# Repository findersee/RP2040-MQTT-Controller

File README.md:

# Controller
<p>RP2040 MQTT Controller for DIN Rail</p>

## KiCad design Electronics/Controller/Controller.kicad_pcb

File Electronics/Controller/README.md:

# Controller
<p>RP2040 Ethernet board</p>

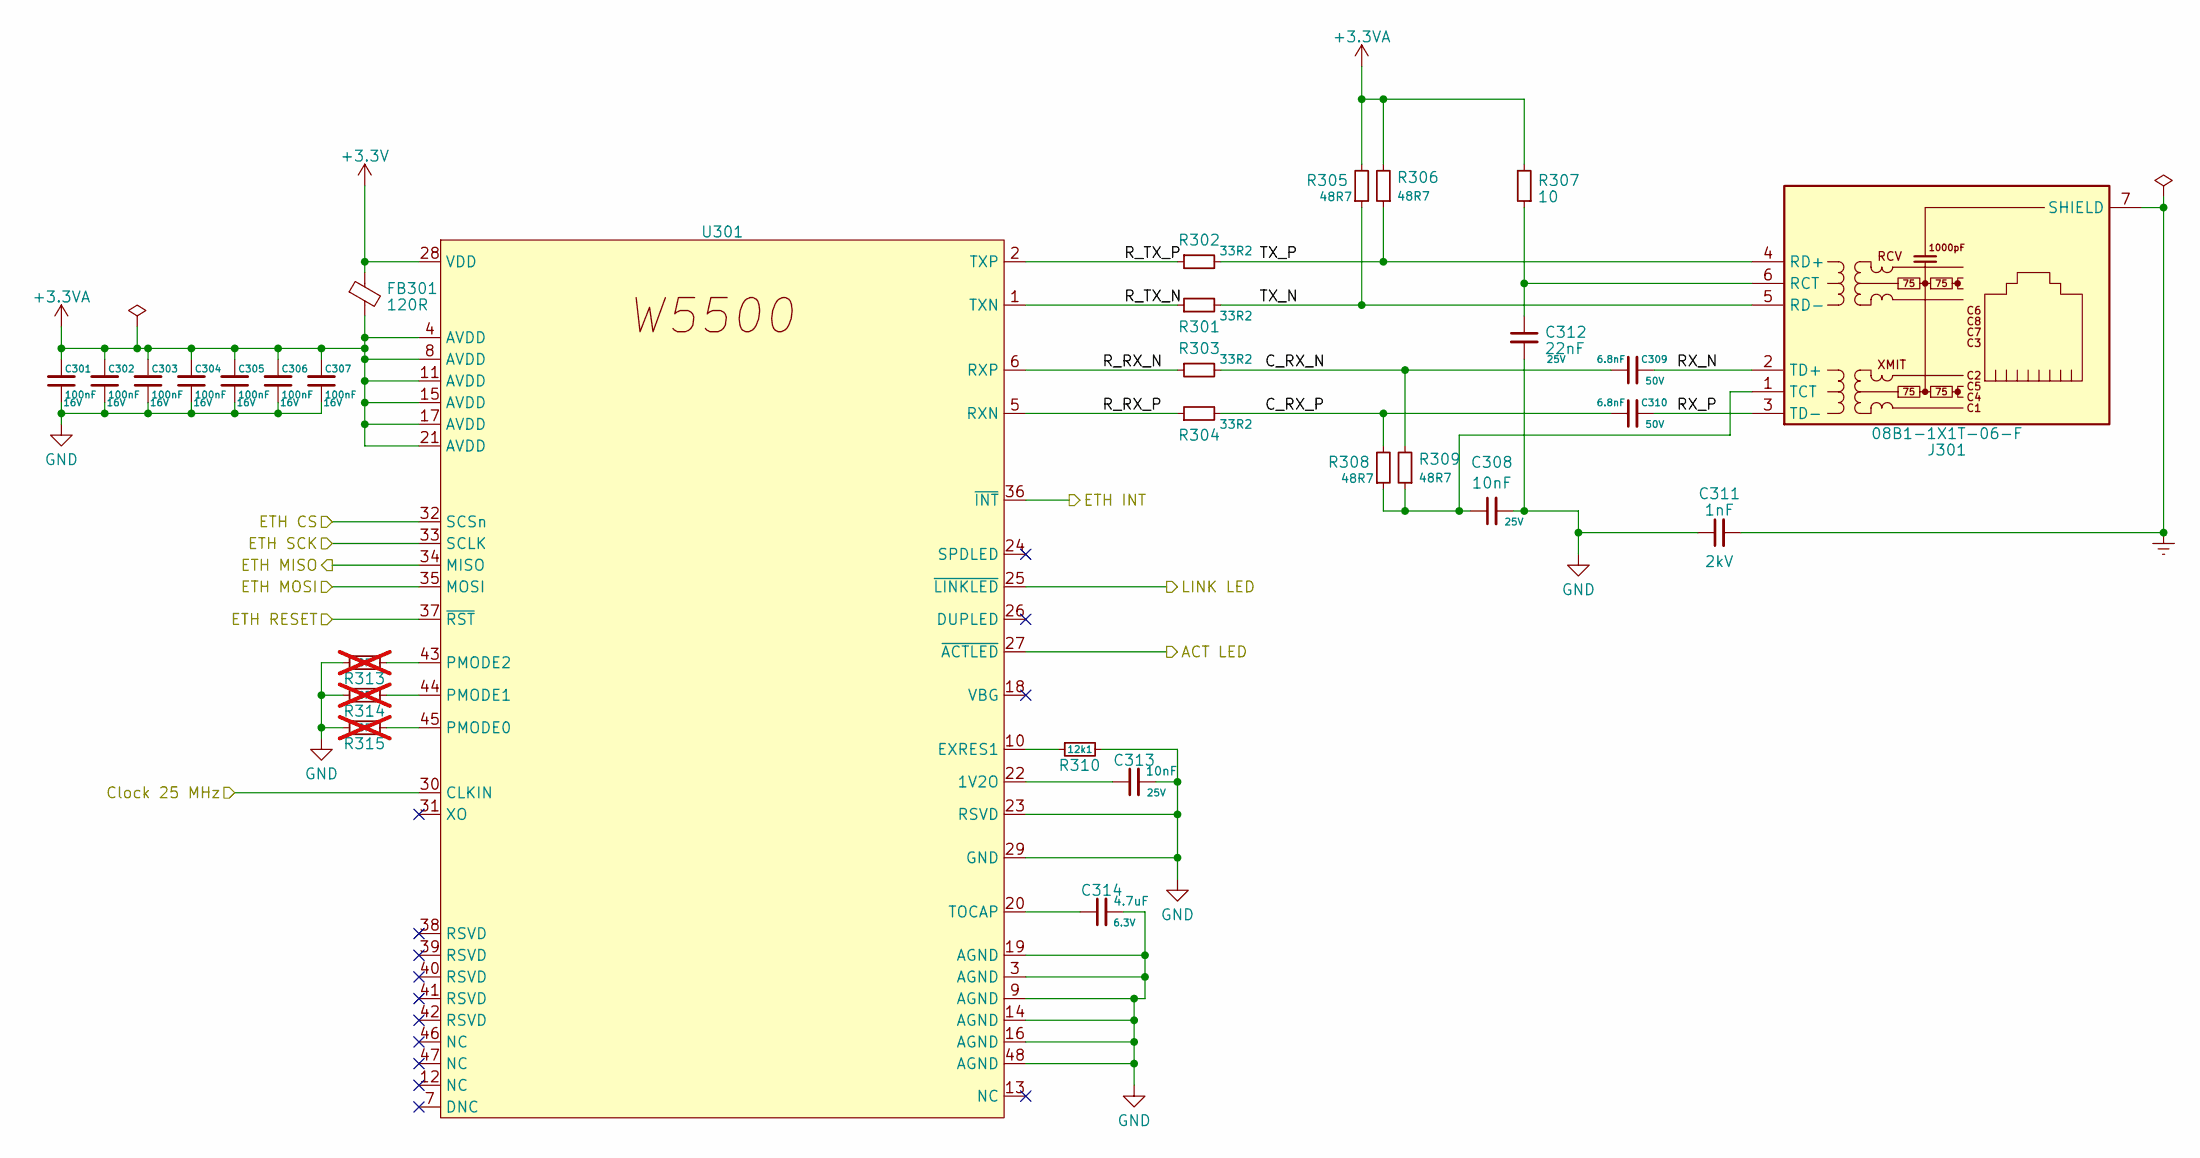
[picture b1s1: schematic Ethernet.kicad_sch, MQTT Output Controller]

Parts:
C301, C302, C303, C304, C305, C306, C307: 100nF; C_0402_1005Metric; Voltage 16V
C308, C313: 10nF; C_0402_1005Metric; Voltage 25V
C309, C310: 6.8nF; C_0402_1005Metric; Voltage 50V
C311: 1nF; C_1206_3216Metric; Voltage 2kV
C312: 22nF; C_0402_1005Metric; Voltage 25V
C314: 4.7uF; C_0402_1005Metric; Voltage 6.3V
FB301: 120R; R_0805_2012Metric
J301: 08B1-1X1T-06-F
R301, R302, R303, R304: 33R2; R_0402_1005Metric
R305, R306, R308, R309: 48R7; R_0402_1005Metric
R307: 10; R_0402_1005Metric
R310: 12k1; R_0402_1005Metric
R313, R314, R315: 0R; R_0402_1005Metric; not fitted
U301: W5500; TQFP-48_7x7mm_P0.5mm

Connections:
+3.3V: FB301.1, U301.28 (VDD); also elsewhere on the board
+3.3VA: C301.2, C302.2, C303.2, C304.2, C305.2, C306.2, C307.2, FB301.2, R305.2, R306.2, R307.2, U301.4 (AVDD), U301.8 (AVDD), U301.11 (AVDD), U301.15 (AVDD), U301.17 (AVDD), U301.21 (AVDD)
/Ethernet/ACT LED: U301.27 (~ACTLED); also elsewhere on the board
/Ethernet/C_RX_N: C309.1, R303.2, R309.2
/Ethernet/C_RX_P: C310.1, R304.2, R308.2
/Ethernet/Clock 25 MHz: U301.30 (CLKIN); also elsewhere on the board
/Ethernet/ETH CS: U301.32 (SCSn); also elsewhere on the board
/Ethernet/ETH INT: U301.36 (~INT); also elsewhere on the board
/Ethernet/ETH MISO: U301.34 (MISO); also elsewhere on the board
/Ethernet/ETH MOSI: U301.35 (MOSI); also elsewhere on the board
/Ethernet/ETH RESET: U301.37 (~RST); also elsewhere on the board
/Ethernet/ETH SCK: U301.33 (SCLK); also elsewhere on the board
/Ethernet/LINK LED: U301.25 (~LINKLED); also elsewhere on the board
/Ethernet/RX_N: C309.2, J301.2 (TD+)
/Ethernet/RX_P: C310.2, J301.3 (TD-)
/Ethernet/R_RX_N: R303.1, U301.6 (RXP)
/Ethernet/R_RX_P: R304.1, U301.5 (RXN)
/Ethernet/R_TX_N: R301.1, U301.1 (TXN)
/Ethernet/R_TX_P: R302.1, U301.2 (TXP)
/Ethernet/TX_N: J301.5 (RD-), R301.2, R305.1
/Ethernet/TX_P: J301.4 (RD+), R302.2, R306.1
Earth: C311.2, J301.7 (SHIELD); also elsewhere on the board
GND: C301.1, C302.1, C303.1, C304.1, C305.1, C306.1, C307.1, C308.2, C311.1, C312.2, C313.2, C314.2, R310.2, R313.1, R314.1, R315.1, U301.3 (AGND), U301.9 (AGND), U301.14 (AGND), U301.16 (AGND), U301.19 (AGND), U301.23 (RSVD), U301.29 (GND), U301.48 (AGND); also elsewhere on the board
unnamed: C312.1, J301.6 (RCT), R307.1
unnamed: C308.1, J301.1 (TCT), R308.1, R309.1
unnamed: C313.1, U301.22 (1V2O)
unnamed: R310.1, U301.10 (EXRES1)
unnamed: R315.2, U301.45 (PMODE0)
unnamed: R314.2, U301.44 (PMODE1)
unnamed: R313.2, U301.43 (PMODE2)
unnamed: C314.1, U301.20 (TOCAP)

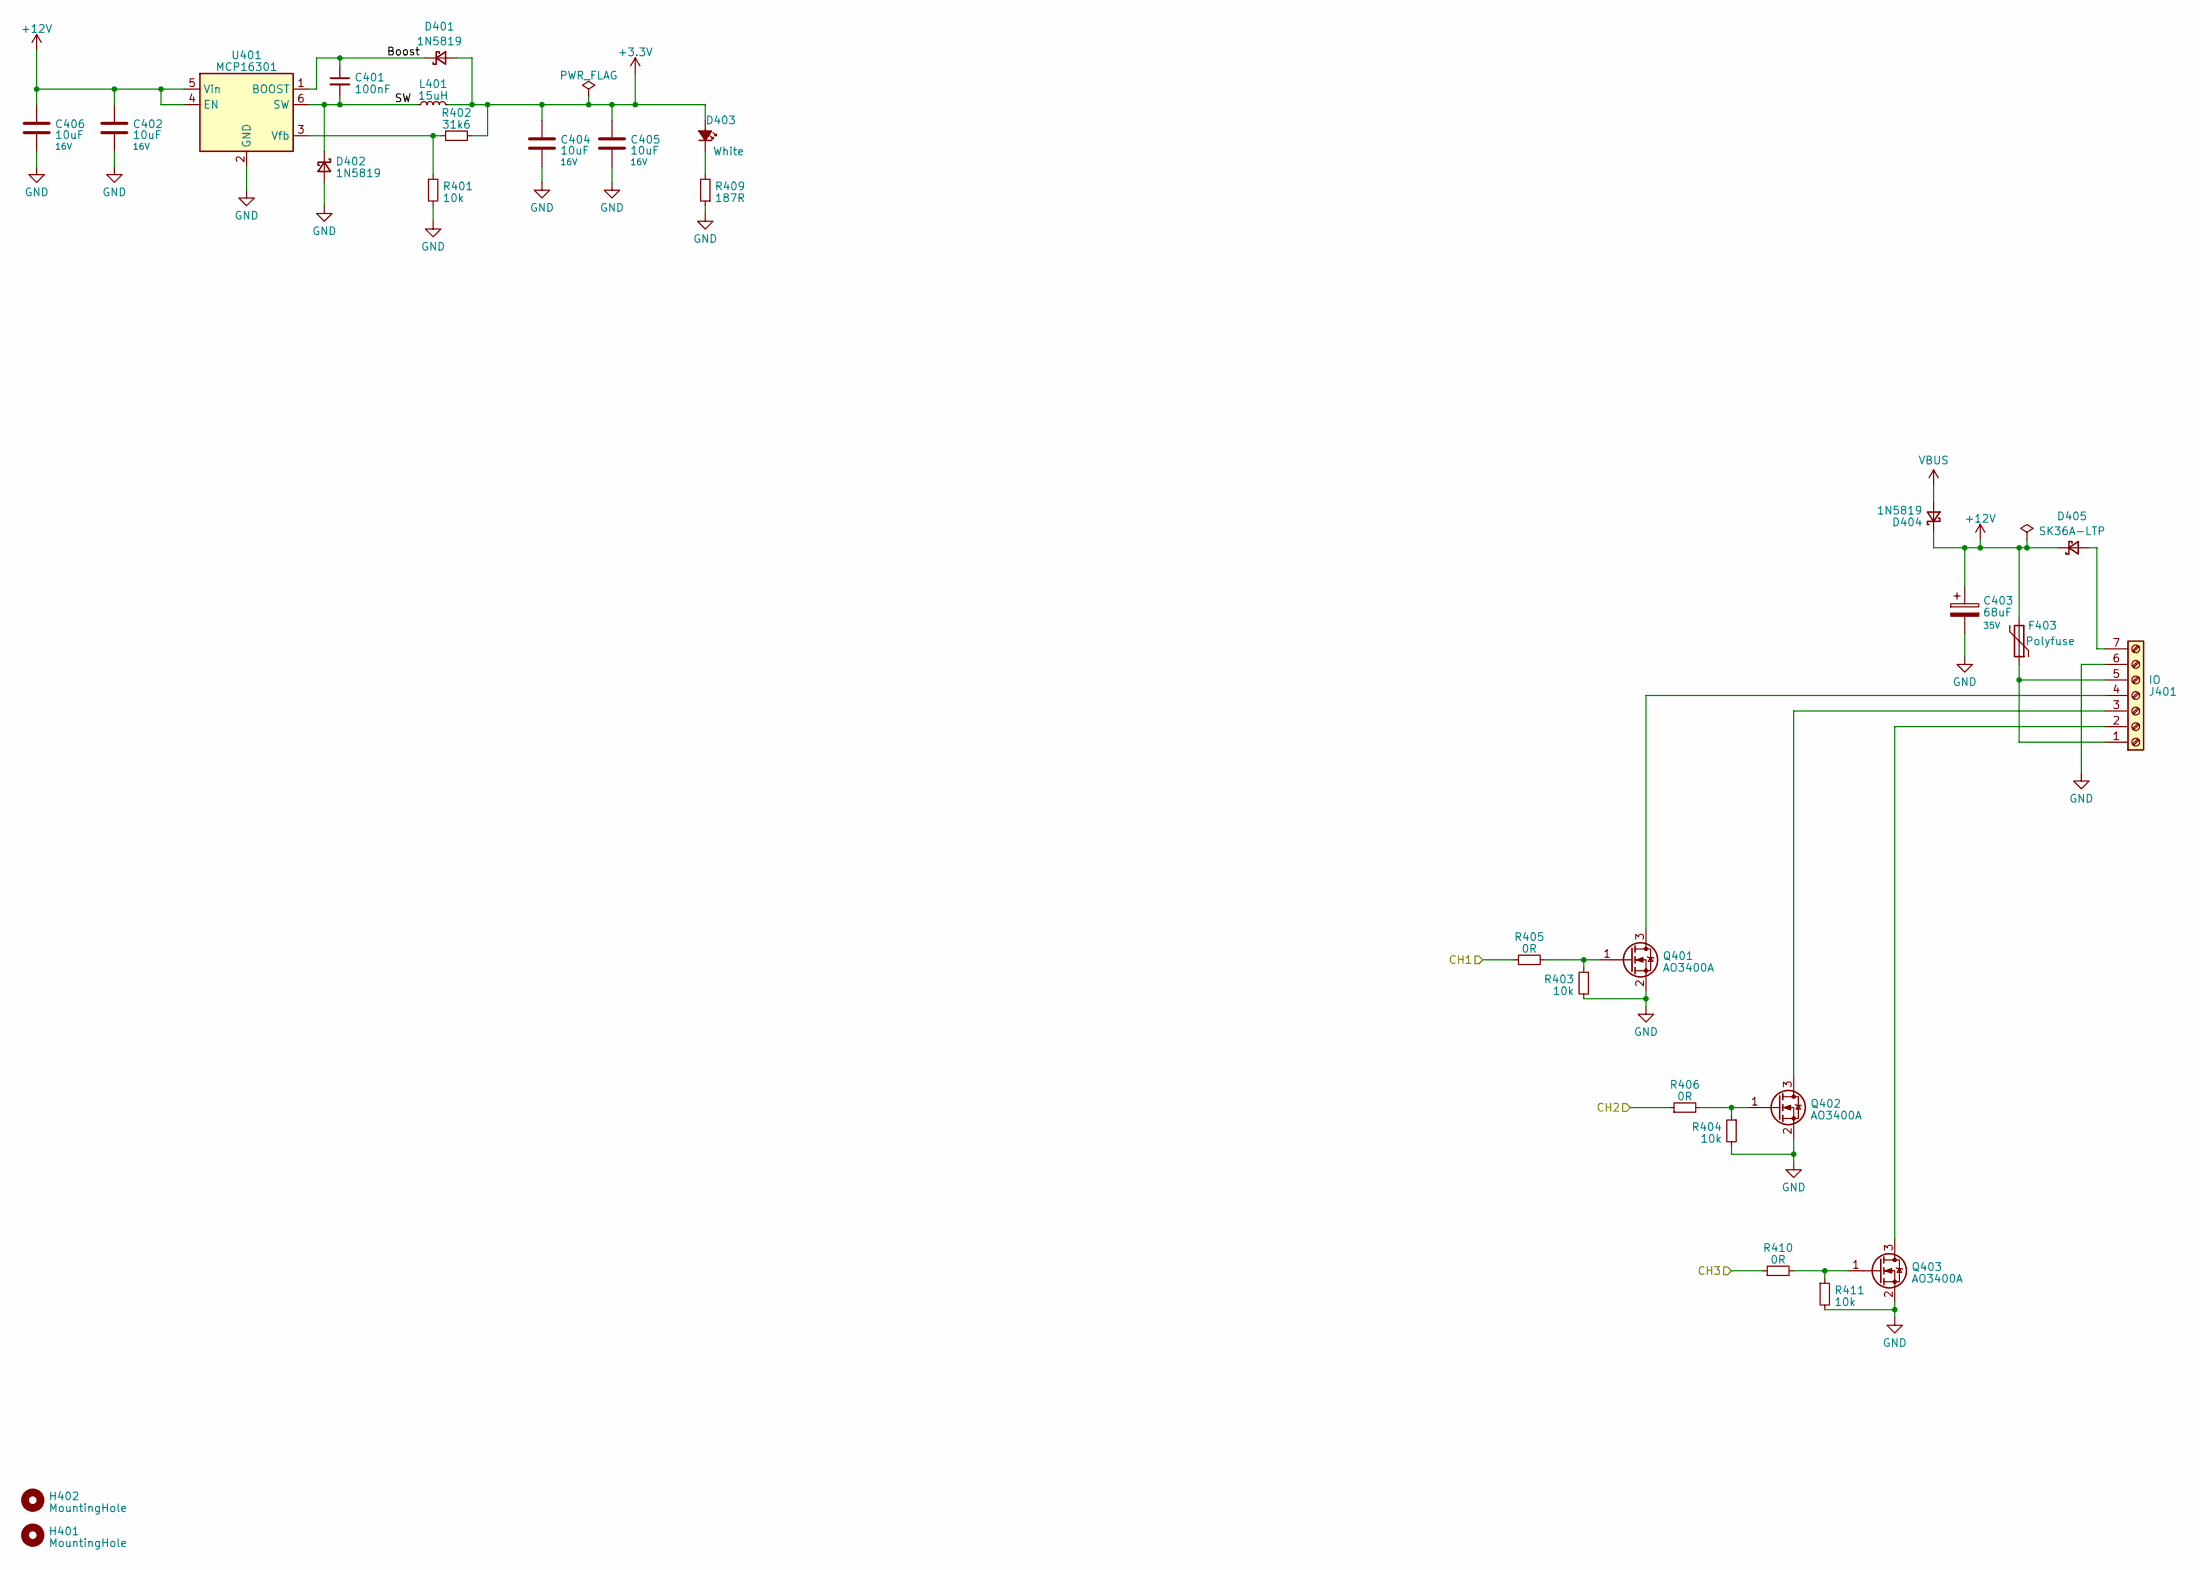
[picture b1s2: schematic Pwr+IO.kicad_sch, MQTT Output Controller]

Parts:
C401: 100nF; C_0402_1005Metric
C402, C404, C405, C406: 10uF; C_0805_2012Metric; Voltage 16V
C403: 68uF; CP_Elec_6.3x5.8; Voltage 35V
D401, D402, D404: 1N5819; D_SOD-123
D403: White; LED_0603_1608Metric
D405: SK36A-LTP; D_SMA
F403: Polyfuse; Fuse_BelFuse_0ZRE0005FF_L8.3mm_W3.8mm
H401, H402: MountingHole; MountingHole_2.5mm
J401: IO; Terminal-Block-01x07_P3.81
L401: 15uH; L_Coilcraft_LPS3010
Q401, Q402, Q403: AO3400A; SOT-23
R401, R403, R404, R411: 10k; R_0402_1005Metric
R402: 31k6; R_0402_1005Metric
R405, R406, R410: 0R; R_0402_1005Metric
R409: 187R; R_0402_1005Metric
U401: MCP16301; SOT-23-6

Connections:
+3.3V: C404.1, C405.1, D401.2 (A), D403.2 (A), L401.2, R402.2; also elsewhere on the board
+12V: C402.1, C403.1, C406.1, D404.1 (K), D405.1 (K), F403.2, U401.4 (EN), U401.5 (Vin)
/Power and Output/Boost: C401.1, D401.1 (K), U401.1 (BOOST)
/Power and Output/CH1: R405.1; also elsewhere on the board
/Power and Output/CH2: R406.1; also elsewhere on the board
/Power and Output/CH3: R410.1; also elsewhere on the board
/Power and Output/SW: C401.2, D402.1 (K), L401.1, U401.6 (SW)
GND: C402.2, C403.2, C404.2, C405.2, C406.2, D402.2 (A), J401.6, Q401.2 (S), Q402.2 (S), Q403.2 (S), R401.2, R403.2, R404.2, R409.1, R411.2, U401.2 (GND); also elsewhere on the board
unnamed: D403.1 (K), R409.2
unnamed: D405.2 (A), J401.7
unnamed: F403.1, J401.1, J401.5
unnamed: J401.2, Q403.3 (D)
unnamed: J401.3, Q402.3 (D)
unnamed: J401.4, Q401.3 (D)
unnamed: Q401.1 (G), R403.1, R405.2
unnamed: Q402.1 (G), R404.1, R406.2
unnamed: Q403.1 (G), R410.2, R411.1
unnamed: R401.1, R402.1, U401.3 (Vfb)
VBUS: D404.2 (A); also elsewhere on the board

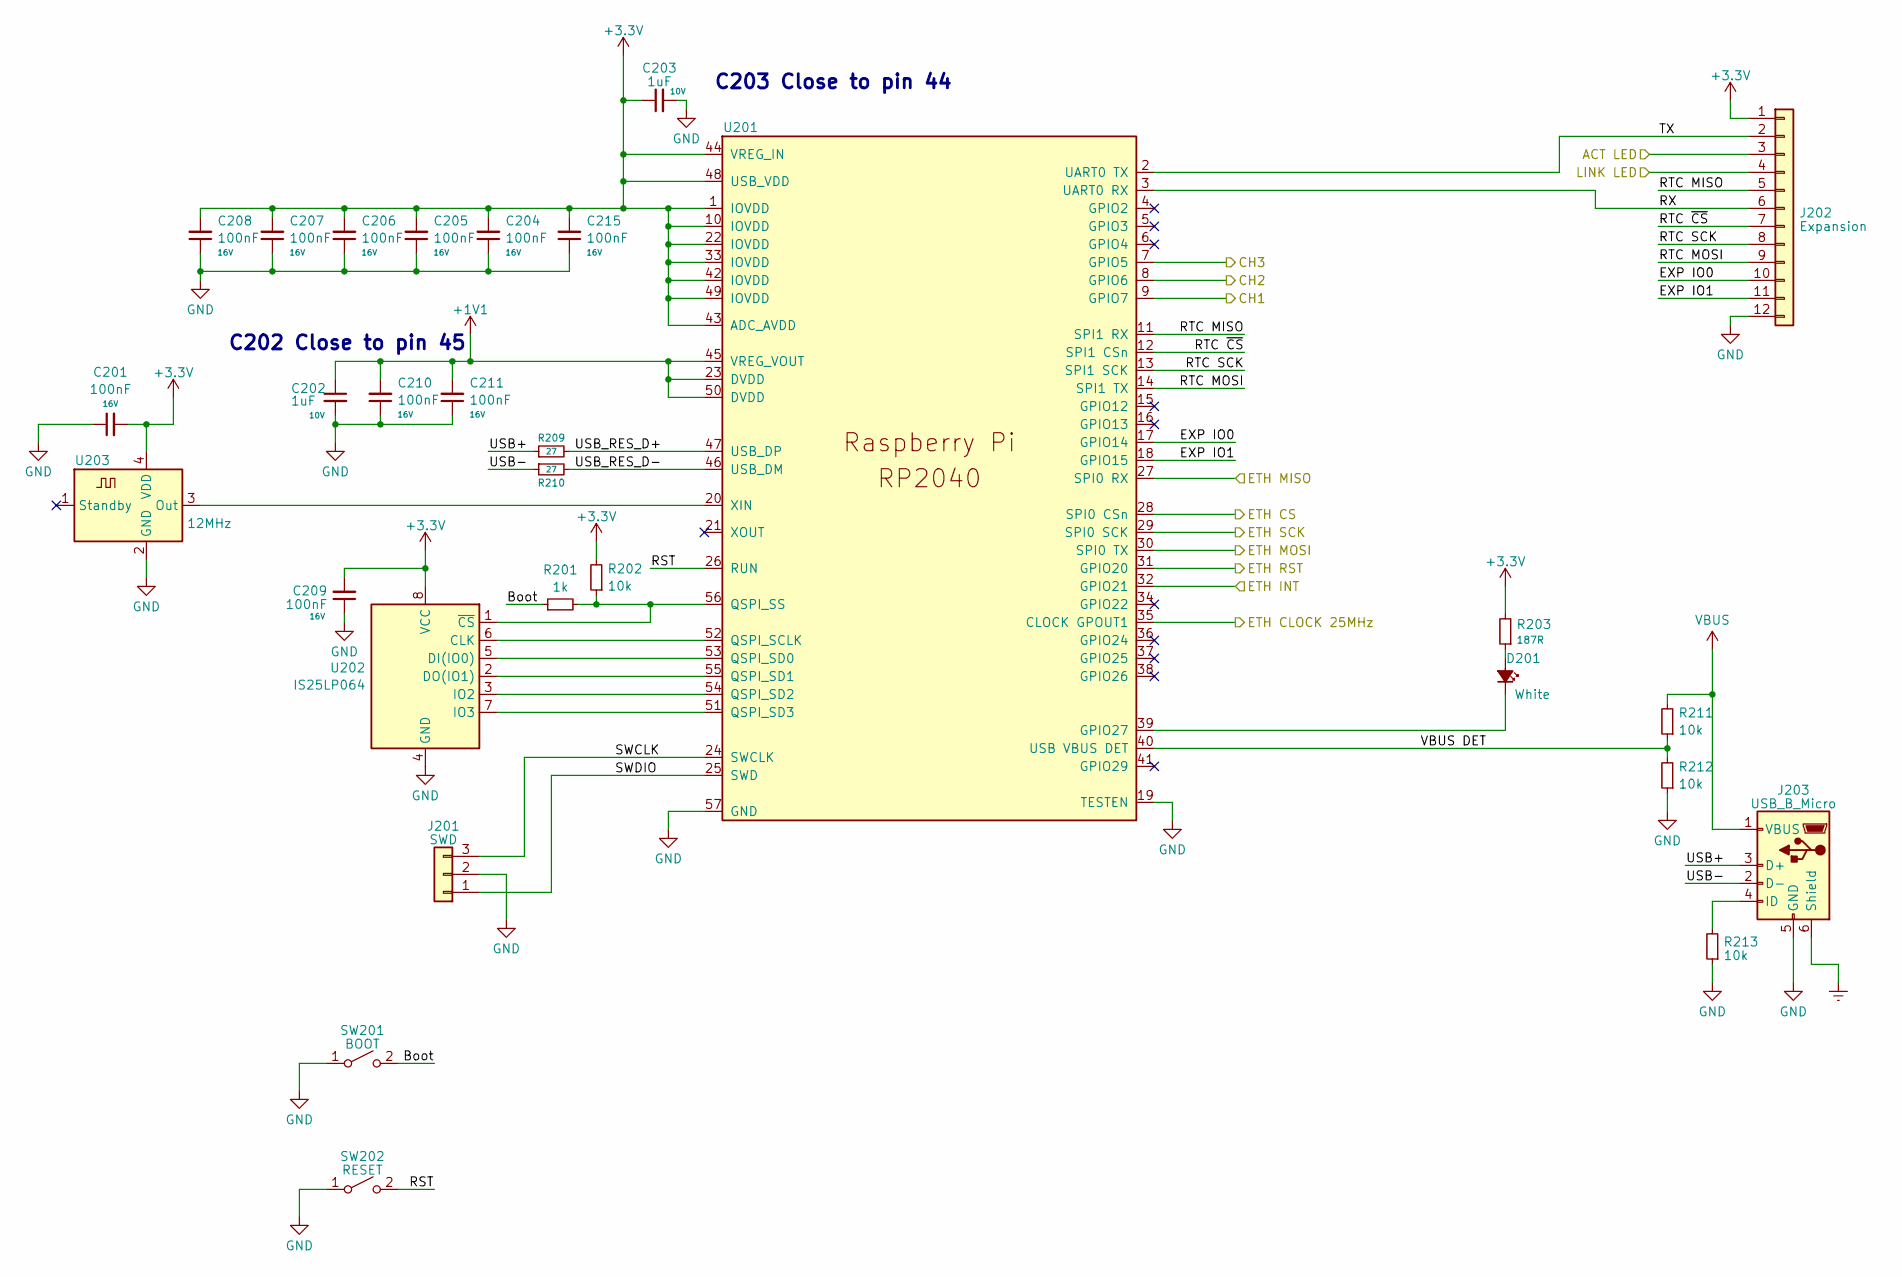
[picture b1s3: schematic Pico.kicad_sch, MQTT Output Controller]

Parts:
C201, C204, C205, C206, C207, C208, C209, C210, C211, C215: 100nF; C_0402_1005Metric; Voltage 16V
C202, C203: 1uF; C_0402_1005Metric; Voltage 10V
D201: White; LED_0603_1608Metric
J201: SWD; PinHeader_1x03_P2.54mm_Vertical
J202: Expansion; PinSocket_2x06_P2.54mm_Vertical
J203: USB_B_Micro; USB_Micro-B_Molex_47346-0001
R201: 1k; R_0402_1005Metric
R202, R211, R212, R213: 10k; R_0402_1005Metric
R203: 187R; R_0402_1005Metric
R209, R210: 27; R_0402_1005Metric
SW201: BOOT; SW_SPST_B3U-1000P
SW202: RESET; SW_SPST_B3U-1000P
U201: RP2040; RP2040-QFN-56
U202: IS25LP064; SOIC-8_5.23x5.23mm_P1.27mm
U203: 12MHz; Oscillator_SMD_SeikoEpson_SG8002CE-4Pin_3.2x2.5mm

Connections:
+1V1: C202.1, C210.2, C211.2, U201.23 (DVDD), U201.45 (VREG_VOUT), U201.50 (DVDD)
+3.3V: C201.2, C203.1, C204.2, C205.2, C206.2, C207.2, C208.2, C209.2, C215.2, J202.1, R202.2, R203.2, U201.1 (IOVDD), U201.10 (IOVDD), U201.22 (IOVDD), U201.33 (IOVDD), U201.42 (IOVDD), U201.43 (ADC_AVDD), U201.44 (VREG_IN), U201.48 (USB_VDD), U201.49 (IOVDD), U202.8 (VCC), U203.4 (VDD); also elsewhere on the board
/Ethernet/ACT LED: J202.3; also elsewhere on the board
/Ethernet/Clock 25 MHz: U201.35 (CLOCK GPOUT1); also elsewhere on the board
/Ethernet/ETH CS: U201.28 (SPI0 CSn); also elsewhere on the board
/Ethernet/ETH INT: U201.32 (GPIO21); also elsewhere on the board
/Ethernet/ETH MISO: U201.27 (SPI0 RX); also elsewhere on the board
/Ethernet/ETH MOSI: U201.30 (SPI0 TX); also elsewhere on the board
/Ethernet/ETH RESET: U201.31 (GPIO20); also elsewhere on the board
/Ethernet/ETH SCK: U201.29 (SPI0 SCK); also elsewhere on the board
/Ethernet/LINK LED: J202.4; also elsewhere on the board
/Power and Output/CH1: U201.9 (GPIO7); also elsewhere on the board
/Power and Output/CH2: U201.8 (GPIO6); also elsewhere on the board
/Power and Output/CH3: U201.7 (GPIO5); also elsewhere on the board
/RP2040/Boot: R201.1, SW201.2 (B)
/RP2040/EXP IO0: J202.10, U201.17 (GPIO14)
/RP2040/EXP IO1: J202.11, U201.18 (GPIO15)
/RP2040/RST: SW202.2 (B), U201.26 (RUN)
/RP2040/RTC MISO: J202.5, U201.11 (SPI1 RX)
/RP2040/RTC MOSI: J202.9, U201.14 (SPI1 TX)
/RP2040/RTC SCK: J202.8, U201.13 (SPI1 SCK)
/RP2040/RTC ~CS: J202.7, U201.12 (SPI1 CSn)
/RP2040/RX: J202.6, U201.3 (UART0 RX)
/RP2040/SWCLK: J201.3, U201.24 (SWCLK)
/RP2040/SWDIO: J201.1, U201.25 (SWD)
/RP2040/TX: J202.2, U201.2 (UART0 TX)
/RP2040/USB+: J203.3 (D+), R209.1
/RP2040/USB-: J203.2 (D-), R210.1
/RP2040/USB_RES_D+: R209.2, U201.47 (USB_DP)
/RP2040/USB_RES_D-: R210.2, U201.46 (USB_DM)
/RP2040/VBUS DET: R211.1, R212.2, U201.40 (USB VBUS DET)
Earth: J203.6 (Shield); also elsewhere on the board
GND: C201.1, C202.2, C203.2, C204.1, C205.1, C206.1, C207.1, C208.1, C209.1, C210.1, C211.1, C215.1, J201.2, J202.12, J203.5 (GND), R212.1, R213.1, SW201.1 (A), SW202.1 (A), U201.19 (TESTEN), U201.57 (GND), U202.4 (GND), U203.2 (GND); also elsewhere on the board
unnamed: D201.2 (A), R203.1
unnamed: D201.1 (K), U201.39 (GPIO27)
unnamed: J203.4 (ID), R213.2
unnamed: U201.52 (QSPI_SCLK), U202.6 (CLK)
unnamed: U201.53 (QSPI_SD0), U202.5 (DI(IO0))
unnamed: U201.55 (QSPI_SD1), U202.2 (DO(IO1))
unnamed: U201.54 (QSPI_SD2), U202.3 (IO2)
unnamed: U201.51 (QSPI_SD3), U202.7 (IO3)
unnamed: R201.2, R202.1, U201.56 (QSPI_SS), U202.1 (~CS)
unnamed: U201.20 (XIN), U203.3 (Out)
VBUS: J203.1 (VBUS), R211.2; also elsewhere on the board

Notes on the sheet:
C202 Close to pin 45
C203 Close to pin 44

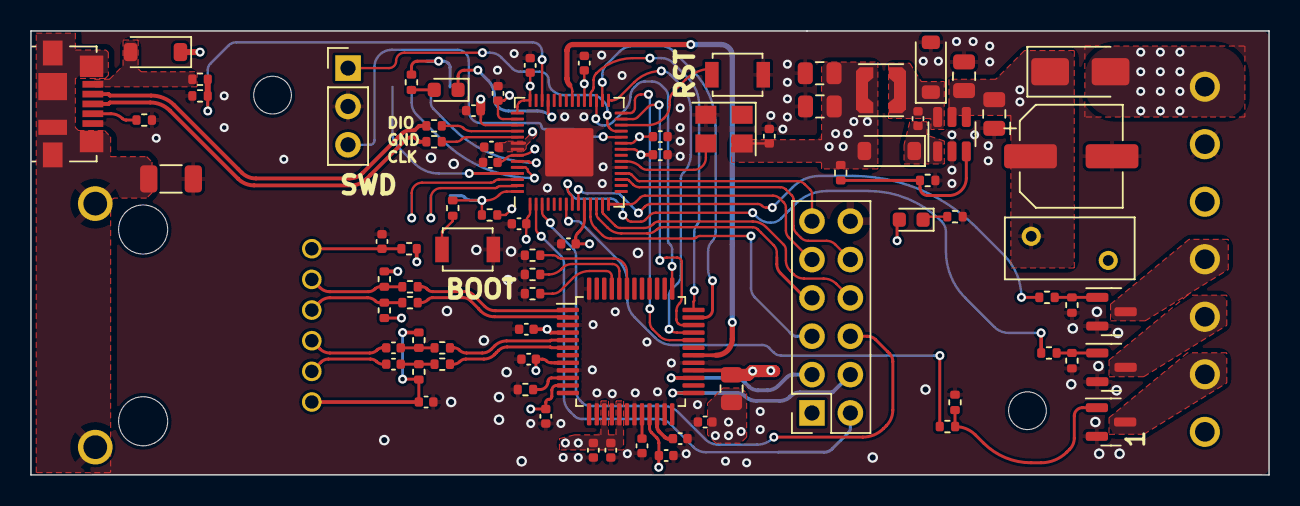
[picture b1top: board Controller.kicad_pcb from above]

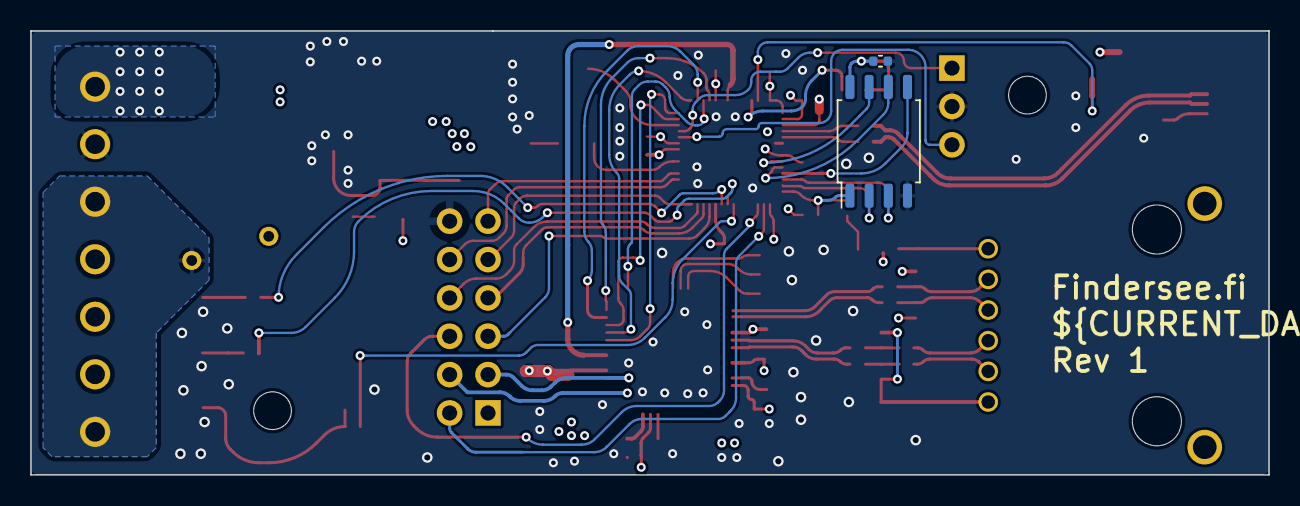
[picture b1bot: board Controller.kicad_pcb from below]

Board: 4 copper layers, 82.0 x 29.4 mm, 88 parts (2 on the bottom side), 76 nets.

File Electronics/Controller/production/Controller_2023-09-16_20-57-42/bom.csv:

Designator,Footprint,Quantity,Value,LCSC Part #
"C201, C204, C205, C206, C207, C208, C209, C210, C211, C215, C301, C302, C303, C304, C305, C306, C315, C401",0402,18,100nF,
"C202, C203",0402,2,1uF,
"C307, C314",0402,2,4.7uF,
"C308, C313",0402,2,10n,
"C309, C310",0402,2,6.8nF,
C311,1206,1,1nF,
C312,0402,1,22nF,
C402,0805,1,10uF,
C403,CP_Elec_6.3x5.8,1,100uF,
"C404, C405",0603,2,10uF,
D401,D_SOD-123,1,1N4148,
D402,D_SOD-123,1, RBR5RSM40BTF,
D403,0805,1,White,
F403,Fuse_BelFuse_0ZRE0005FF_L8.3mm_W3.8mm,1,Polyfuse,
"FB301, FB401",0805,2,120R,
"H401, H402",MountingHole_3.2mm_M3_DIN965,2,MountingHole,
J201,PinHeader_2x02_P2.54mm_Vertical,1,SWD,
J202,PinSocket_2x06_P2.54mm_Vertical,1,Expansion,
J203,USB_Micro-B_Molex_47346-0001,1,USB_B_Micro,
J301,08B1-1X1T-06-F,1,08B1-1X1T-06-F,
J401,Terminal-Block-01x07_P3.81,1,IO,
JP1,0402_Jumper_3pin,1,CLK JUMPER,
L401,L_Coilcraft_LPS3010,1,15uH,
"Q401, Q402, Q403",SOT-23,3,AO3400A,
R201,0402,1,1k,
"R301, R302, R303, R304",0402,4,33,
"R305, R306, R308, R309",0402,4,50,
R307,0402,1,10,
R310,0402,1,12k4,
"R401, R403, R404, R411",0402,4,10k,
R402,0402,1,31k6,
"R405, R406, R410",0402,3,0R,
R409,0402,1,180,
SW201,SW_SPST_B3U-1000P,1,BOOT,
SW202,SW_SPST_B3U-1000P,1,RESET,
U201,RP2040-QFN-56,1,RP2040,
U202,SOIC-8_5.23x5.23mm_P1.27mm,1,W25Q32JVSS,
U203,Oscillator_SMD_Abracon_ASDMB-4Pin_2.5x2.0mm,1,ASDMB-12.000MHZ-LC-T,
U301,TQFP-48_7x7mm_P0.5mm,1,W5500,
U302,Oscillator_SMD_Abracon_ASDMB-4Pin_2.5x2.0mm,1,ASDMB-25.000MHZ-LC-T,
U401,SOT-23-6,1,MCP16301,

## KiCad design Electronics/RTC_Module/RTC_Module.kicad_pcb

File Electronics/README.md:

# Controller
<p>RP2040 Ethernet board</p>

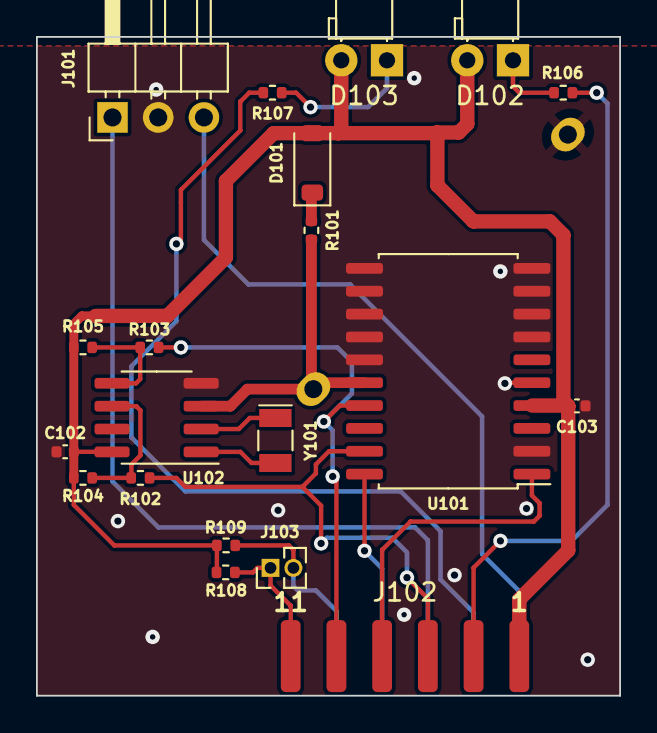
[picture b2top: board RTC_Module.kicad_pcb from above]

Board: 2 copper layers, 32.4 x 36.6 mm, 21 parts (1 on the bottom side), 20 nets.

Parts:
C101: 0.47F; EECS5R5474
C102, C103: 1u; C_0402_1005Metric
D101: 1N5819; D_SOD-123
D102: GREEN; LED_D3.0mm_Horizontal_O1.27mm_Z2.0mm
D103: RED; LED_D3.0mm_Horizontal_O1.27mm_Z2.0mm
J101: EXT_UART; PinHeader_1x03_P2.54mm_Horizontal
J102: Expansion; 02x06_SMD_2.54mm
J103: EXP I^{2}C; PinHeader_1x02_P1.27mm_Vertical
R101: 100R; R_0402_1005Metric
R102, R103: 0R; R_0402_1005Metric
R104, R105, R106, R107, R108, R109: 4k7; R_0402_1005Metric
U101: DS3234S; SOIC-20W_7.5x12.8mm_P1.27mm
U102: DS1307ZN+; SOIC-8_3.9x4.9mm_P1.27mm
Y101: 32.768k; Crystal_SMD_MicroCrystal_CC7V-T1A-2Pin_3.2x1.5mm

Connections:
+3.3V: C102.2, C103.2, D101.2 (A), D102.2 (A), D103.2 (A), J102.1, R104.1, R105.1, R108.2, R109.1, U101.4 (VCC), U102.8 (VCC)
+BATT: C101.1, R101.2, U101.16 (VBAT), U102.3 (VBAT)
/IO 1: J102.10, J103.2, R108.1, U101.5 (~INT)
/IO 2: J102.11, J103.1, R109.2
/LED1: J102.3, R106.1
/LED2: J102.4, R107.1
/RTC MISO: J102.5, R102.1, U101.19 (DOUT)
/RTC MOSI: J102.9, R103.1, U101.17 (DIN)
/RTC SCK: J102.8, U101.20 (SCLK)
/RTC ~CS: J102.7, U101.1 (~CS)
/RX: J101.1, J102.6
/TX: J101.3, J102.2
GND: C101.2, C102.1, C103.1, J101.2, J102.12, U101.2 (N.C), U101.7 (N.C), U101.8 (N.C), U101.9 (N.C), U101.10 (N.C), U101.11 (N.C), U101.12 (N.C), U101.13 (N.C), U101.14 (N.C), U101.15 (GND), U102.4 (GND)
unnamed: D101.1 (K), R101.1
unnamed: D102.1 (K), R106.2
unnamed: D103.1 (K), R107.2
unnamed: R102.2, R104.2, U102.6 (SCL)
unnamed: R103.2, R105.2, U102.5 (SDA)
unnamed: U102.1 (X1), Y101.2
unnamed: U102.2 (X2), Y101.1

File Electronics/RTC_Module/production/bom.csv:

Designator,Footprint,Quantity,Value,LCSC Part #
C101,EECS5R5474,1,0.47F,
C102,0402,1,1u,
D101,D_SOD-123,1, RBR5RSM40BTF,
D102,LED_D1.8mm_W1.8mm_H2.4mm_Horizontal_O1.27mm_Z1.6mm,1,GREEN,
D103,LED_D1.8mm_W1.8mm_H2.4mm_Horizontal_O1.27mm_Z1.6mm,1,RED,
J101,PinHeader_1x03_P2.54mm_Horizontal,1,EXT_UART,
J102,02x06_SMD_2.54mm,1,Expansion,
J103,PinHeader_1x02_P1.27mm_Vertical,1,EXP I^{2}C,
U101,SOIC-20W_7.5x12.8mm_P1.27mm,1,DS3234S,

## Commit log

2023-09-15 Electronics Commit
2023-09-16 Added RTC Module And Step models for PCBs
2023-09-16 PDF Update
2023-09-16 Removed Production folders
2023-09-17 Manufacturing Commit
2023-09-17 Added Controller README.md
2023-09-17 Fixed readme
2023-09-17 Readme fix 2
2023-09-17 Added Readme images
2023-09-17 Readme image fixes
2023-09-19 Manufacturing commit 2
2023-09-21 Software addition commit
2023-09-25 Created DS3234 RTC IC Driver
2023-09-25 Removed not used pico-extras submodule
2023-09-26 Improved DS3234 Driver Added microjson to the project
2023-09-27 Created Uptime task Created first prototype of json messages
2023-10-02 Creating settings logic for relay array
2023-10-02 Added Temperature info to the uptime MQTT publish
2023-10-14 Pin goof fix
2023-10-17 DS3234_Driver Fixes Added watch dog reset
2023-11-02 Added library Fixed layout bugs Software improvements
2023-11-23 Changed Topic to use device serial
2024-01-11 Schematic and Layout update
2024-02-19 Improvements
